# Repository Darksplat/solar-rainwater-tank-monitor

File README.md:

**Fabrication correction — 11 November 2026.** Review found that LOOP_P named both the pressure-probe terminal and the filtered positive measurement input in revision 0.2. This can bypass part of the current-limiting network through a sense resistor. The revision 0.2 PCB and manufacturing exports are superseded and require correction before fabrication. Revision 0.3 development separates the input as LOOP_SENSE_P and adds an explicit netlist check.

# Solar rainwater tank monitor

Development revision 0.2, 9 November 2026. **Engineering prototype; not released for manufacture or installation.** Two independent solar nodes; ESP32-C6, Thread MTD, pressure-loop measurement, ESPHome API to Home Assistant.

The revision includes a routed four-layer KiCad board, ERC/DRC reports, fabrication exports, FreeCAD assembly study, three-monitor firmware and battery/solar alerts. Start with [progress register](docs/progress.md), [architecture](docs/project-overview.md), [research evidence](docs/research.md) and [test report](docs/testing-report.md). Outstanding approvals, missing measurements and physical validation are explicit there. No live Home Assistant system has been modified.

Run `python3 -m unittest discover -s tests/unit -v`, then `python3 tools/power_budget.py`. Compile the shared C++ calculation tests with `c++ -std=c++17 -Wall -Wextra -Werror tests/integration/core_test.cpp -o /tmp/tank-core-test && /tmp/tank-core-test`.

Firmware: copy `firmware/secrets-example.yaml` to ignored `firmware/tank_1/secrets.yaml` and `firmware/tank_2/secrets.yaml`, setting independent real API keys and OTA passwords plus your Thread dataset, then `esphome config firmware/tank_1/tank.yaml` and `esphome compile firmware/tank_1/tank.yaml`; repeat for tank_2. Example secrets are deliberately not deployable credentials. See the installation guide before connecting any transmitter.

No rated capacity is treated as measured usable capacity. Configuration is initially uncalibrated and litres/percentage remain unavailable until calibration is enabled.

Build hardware with the [assembly guide](docs/assembly-guide.md), [electrical connection table](docs/electrical-design.md) and [manufacturing notes](hardware/pcb/manufacturing/README.md). Revision 0.1 binaries and wiring are historical and incompatible with revision 0.2.

Owner configuration is recorded in [site settings](docs/site-configuration.md): garden water, secondary fire use, no minimum-reserve display, catalogue tank height2.32m and the existing Raspberry Pi Zero2W/PoE/Sonoff Thread network. Internal geometry and operating datums remain unverified.

[Revision0.2 test images and checksums](releases/0.2.0-dev/) and [successful hosted validation](docs/publication-validation.md) are available. These are development artifacts; physical hardware and installation acceptance remain pending.

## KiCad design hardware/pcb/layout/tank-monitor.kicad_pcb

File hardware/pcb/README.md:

# PCB release hold

No valid complete schematic, layout, Gerber, drill, CPL or board 3D file exists in this revision. Directories reserve the requested structure. Do not mistake their presence for deliverables.

KiCad CLI 10.0.3 is installed. Live IPC was unavailable. This does not itself prevent offline design; current blockers are incomplete protected input/power design, final component qualification and footprint verification. Do not export an outline-only board and claim it is manufacturable.

Next: select protected receiver and power converters, obtain sensor order drawing, assign every pin/net, complete loop and power fault analysis, create manufacturer-backed symbol/footprint library, draw schematic, run ERC, route layout with antenna keepout, run DRC/unconnected checks, then export fabrication and assembly package and prototype.

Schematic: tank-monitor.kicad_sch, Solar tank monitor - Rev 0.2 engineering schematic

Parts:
C1: 10u 50V X7R; C_1210_3225Metric; MPN C3225X7R1H106K250AC
C2: 100n 50V; C_0603_1608Metric; MPN C1608X7R1H104K080AA
C3: 100n 16V; C_0603_1608Metric; MPN C1608X7R1H104K080AA
C4, C5: 22u 16V X7R; C_1210_3225Metric; MPN C3225X7R1C226M250AC
C6: 4.7u 16V X7R; C_0805_2012Metric; MPN C2012X7R1C475K125AB
C7: 4.7u 50V X7R; C_1210_3225Metric; MPN C3225X7R1H475K250AB
C8: 10n; C_0603_1608Metric; MPN C1608X7R1H103K080AA
C20, C30, C40: 100n 100V; C_0805_2012Metric; MPN C2012X7R2A104K125AA
C21, C31, C41, C52: 100n; C_0603_1608Metric; MPN C1608X7R1H104K080AA
C50: 1u; C_0603_1608Metric; MPN C1608X7R1C105K080AC
C51: 10u 35V X5R; C_0805_2012Metric; MPN C2012X5R1V106K085AC
D1, D3: B360A-13-F; D_SMA; MPN B360A-13-F
D2: SMBJ15A; D_SMB; MPN SMBJ15A
D4: SMBJ18A; D_SMB; MPN SMBJ18A
D5, D6, D7: SMBJ51A; D_SMB; MPN SMBJ51A
D8: STATUS; LED_0603_1608Metric; MPN LTST-C190KGKT
D9: 1N5408; 1N5408_DO201AD_P20.32; MPN 1N5408-E3/54
D10: 1N4148W-7-F; D_SOD-123; MPN 1N4148W-7-F
J1: BATTERY FUSED 5A; TerminalBlock_Phoenix_MKDS-1,5-2-5.08_1x02_P5.08mm_Horizont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; MPN Phoenix 1715721
J2: CHARGER BAT; TerminalBlock_Phoenix_MKDS-1,5-2-5.08_1x02_P5.08mm_Horizont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; MPN Phoenix 1715721
J3: PROTECTED LOAD; TerminalBlock_Phoenix_MKDS-1,5-2-5.08_1x02_P5.08mm_Horizont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; MPN Phoenix 1715721
J4: PV INPUT; TerminalBlock_Phoenix_MKDS-1,5-2-5.08_1x02_P5.08mm_Horizont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; MPN Phoenix 1715721
J5: CHARGER PV; TerminalBlock_Phoenix_MKDS-1,5-2-5.08_1x02_P5.08mm_Horizont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; MPN Phoenix 1715721
J6: PRESSURE LOOP; TerminalBlock_Phoenix_MKDS-1,5-2-5.08_1x02_P5.08mm_Horizont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; MPN Phoenix 1715721
J7: UART 3.3V ONLY; PinHeader_1x06_P2.54mm_Vertical; MPN TSW-106-07-G-S
L1: 4.7uH Isat>=4A; L_Bourns_SRP5030T; MPN SRP5030TA-4R7M
L2: 10uH Isat>=1.6A; L_Bourns_SRP5030T; MPN SRP5030TA-100M
Q1: DMP2035U-7; SOT-23; MPN DMP2035U-7
Q2, Q3: IPD50N06S4L-12; TO-252-2; MPN IPD50N06S4L12ATMA2
Q4: BC847B-7-F; SOT-23; MPN BC847B-7-F
R1: 0.01R 1% 1W; R_2512_6332Metric; MPN WSL2512R0100FEA
R2: 0.02R 1% 1W; R_2512_6332Metric; MPN WSL2512R0200FEA
R3, R4, R5, R10, R65, R66: 100k; R_0603_1608Metric; MPN RC0603FR-07100KL
R6: 1k; R_0603_1608Metric; MPN RC0603FR-071KL
R7: 130k 0.1%; R_0603_1608Metric; MPN RT0603BRD07130KL
R8: 10k 0.1%; R_0603_1608Metric; MPN RT0603BRD0710KL
R9: 4.99k; R_0603_1608Metric; MPN RC0603FR-074K99L
R11: 2R 0.1% 25ppm; R_1206_3216Metric; MPN RT1206BRD072RL
R12, R13: 110R 1.5W; R_2512_6332Metric; MPN CRCW2512110RFKEGHP
R20, R21, R22, R40, R41, R42: 10R; R_0603_1608Metric; MPN RC0603FR-0710RL
R30, R31, R32: 47R; R_0603_1608Metric; MPN RC0603FR-0747RL
R50, R51: 4.7k; R_0603_1608Metric; MPN RC0603FR-074K7L
R52, R53, R54, R64, R67: 10k; R_0603_1608Metric; MPN RC0603FR-0710KL
R55: 2.2k; R_0603_1608Metric; MPN RC0603FR-072K2L
R60: 2.74M; R_0603_1608Metric; MPN RC0603FR-072M74L
R61: 215k; R_0603_1608Metric; MPN RC0603FR-07215KL
R62: 84.5k; R_0603_1608Metric; MPN RC0603FR-0784K5L
R63: 510k; R_0603_1608Metric; MPN RC0603FR-07510KL
SW1: RESET; SW_SPST_TL3342; MPN TL3342F160QG-TR
SW2: BOOT; SW_SPST_TL3342; MPN TL3342F160QG-TR
TP1: GND; TestPoint_Pad_D2.0mm
TP2: V3V3; TestPoint_Pad_D2.0mm
TP3: VIN; TestPoint_Pad_D2.0mm
TP4: LOOP_SUPPLY; TestPoint_Pad_D2.0mm
TP5: LOOP_P; TestPoint_Pad_D2.0mm
TP6: SDA; TestPoint_Pad_D2.0mm
TP7: SCL; TestPoint_Pad_D2.0mm
TP8: BAT_FUSED; TestPoint_Pad_D2.0mm
TP9: CHARGER_BAT; TestPoint_Pad_D2.0mm
TP10: PV_IN; TestPoint_Pad_D2.0mm
TP11: PV_OUT; TestPoint_Pad_D2.0mm
TP12: LOOP_EN_N; TestPoint_Pad_D2.0mm
U1: AP63203WU-7; TSOT-23-6; MPN AP63203WU-7
U2: TPS61170DRVR; WSON-6-1EP_2x2mm_P0.65mm_EP1x1.6mm; MPN TPS61170DRVR
U3, U4, U5: INA228AIDGSR; TSSOP-10_3x3mm_P0.5mm; MPN INA228AIDGSR
U6: ESP32-C6-MINI-1-N4; ESP32-C6-MINI-1-edge-silk; MPN ESP32-C6-MINI-1-N4
U7: LTC4365ITS8#TRMPBF; TSOT-23-8; MPN LTC4365ITS8#TRMPBF

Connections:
BAT_FUSED: Q3.2 (D), R1.1, R20.1, R22.1, TP8.1, U7.7 (Vout)
BAT_N: C20.2, R21.2, U3.9 (Vin-)
BAT_P: C20.1, R20.2, U3.10 (Vin+)
BAT_RAW: J1.1, Q2.2 (D), R60.1, R63.1, R65.1, U7.1 (Vin)
BAT_VBUS: R22.2, U3.8 (Vbus)
BOOST_GATE: Q1.1 (G), R5.1, R6.2
BOOST_IN: C6.1, L2.1, Q1.3 (D), U2.5 (CTRL), U2.6 (VIN)
BOOT: J7.5, R53.2, SW2.1, U6.23 (IO9)
BST: C3.1, U1.6 (BST)
CHARGER_BAT: J2.1, R1.2, R21.1, TP9.1
COMP: R9.1, U2.2 (COMP)
COMP_RC: C8.1, R9.2
EN: C50.1, J7.6, R52.2, SW1.1, U6.8 (EN)
EN_BUCK: R3.2, R4.1, U1.2 (EN)
FB_BOOST: R7.2, R8.1, U2.1 (FB)
GND: C1.2, C2.2, C4.2, C5.2, C6.2, C7.2, C8.2, C21.2, C31.2, C41.2, C50.2, C51.2, C52.2, D2.2 (A), D4.2 (A), D5.2 (A), D6.2 (A), D7.2 (A), D10.2 (A), J1.2, J2.2, J3.2, J6.2, J7.1, Q4.2 (E), R4.2, R8.2, R10.2, R62.2, R67.2, SW1.2, SW2.2, TP1.1, U1.4 (GND), U2.3 (GND), U2.7 (PAD), U3.1 (A1), U3.2 (A0), U3.7 (GND), U4.1 (A1), U4.7 (GND), U5.1 (A1), U5.7 (GND), U6.1 (GND), U6.2 (GND), U6.11 (GND), U6.14 (GND), U6.36 (GND), U6.37 (GND), U6.38 (GND), U6.39 (GND), U6.40 (GND), U6.41 (GND), U6.42 (GND), U6.43 (GND), U6.44 (GND), U6.45 (GND), U6.46 (GND), U6.47 (GND), U6.48 (GND), U6.49 (GND), U6.50 (GND), U6.51 (GND), U6.52 (GND), U6.53 (GND), U7.4 (GND)
LED_A: D8.2 (A), R55.2
LED_K: D8.1 (K), U6.24 (IO18)
LOAD_IN: D1.2 (A), J3.1
LOOP_EN_N: R6.1, TP12.1, U6.9 (IO4)
LOOP_LIMIT_MID: R12.2, R13.1
LOOP_N: C40.2, R41.2, U5.9 (Vin-)
LOOP_P: C40.1, J6.1, R13.2, R40.2, R42.1, TP5.1, U5.10 (Vin+)
LOOP_SHUNT_OUT: R11.2, R12.1, R41.1
LOOP_SUPPLY: C7.1, D3.1 (K), D4.1 (K), R7.1, R10.1, R11.1, R40.1, TP4.1
LOOP_VBUS: R42.2, U5.8 (Vbus)
PV_IN: D9.1 (K), R2.1, R30.1, TP10.1
PV_N: C30.2, D6.1 (K), R31.2, U4.9 (Vin-)
PV_NEG: J4.2, J5.2
PV_OUT: J5.1, R2.2, R31.1, R32.1, TP11.1
PV_P: C30.1, D5.1 (K), R30.2, U4.10 (Vin+)
PV_RAW: D9.2 (A), J4.1
PV_VBUS: D7.1 (K), R32.2, U4.8 (Vbus)
RAW_BASE: D10.1 (K), Q4.1 (B), R65.2, R67.1
RAW_PRESENT: Q4.3 (C), R66.2, U6.26 (IO20)
REV_FAULT: R64.2, U6.25 (IO19), U7.6 (~FAULT)
REV_GATE: Q2.1 (G), Q3.1 (G), U7.8 (GATE)
REV_OV: R61.2, R62.1, U7.3 (OV)
REV_SHDN: R63.2, U7.5 (~SHDN)
REV_SOURCE: Q2.3 (S), Q3.3 (S)
REV_UV: R60.2, R61.1, U7.2 (UV)
RXD: J7.4, U6.30 (RXD0)
SCL: R51.2, TP7.1, U3.5 (SCL), U4.5 (SCL), U5.5 (SCL), U6.16 (IO7)
SDA: R50.2, TP6.1, U3.4 (SDA), U4.4 (SDA), U5.2 (A0), U5.4 (SDA), U6.15 (IO6)
STRAP8: R54.2, U6.22 (IO8)
SW_BOOST: D3.2 (A), L2.2, U2.4 (SW)
SW_BUCK: C3.2, L1.1, U1.5 (SW)
TXD: J7.3, U6.31 (TXD0)
V3V3: C4.1, C5.1, C21.1, C31.1, C41.1, C51.1, C52.1, J7.2, L1.2, Q1.2 (S), R5.2, R50.1, R51.1, R52.1, R53.1, R54.1, R55.1, R64.1, R66.1, TP2.1, U1.1 (FB), U3.6 (VS), U4.2 (A0), U4.6 (VS), U5.6 (VS), U6.3 (3V3)
VIN: C1.1, C2.1, D1.1 (K), D2.1 (K), R3.1, TP3.1, U1.3 (IN)

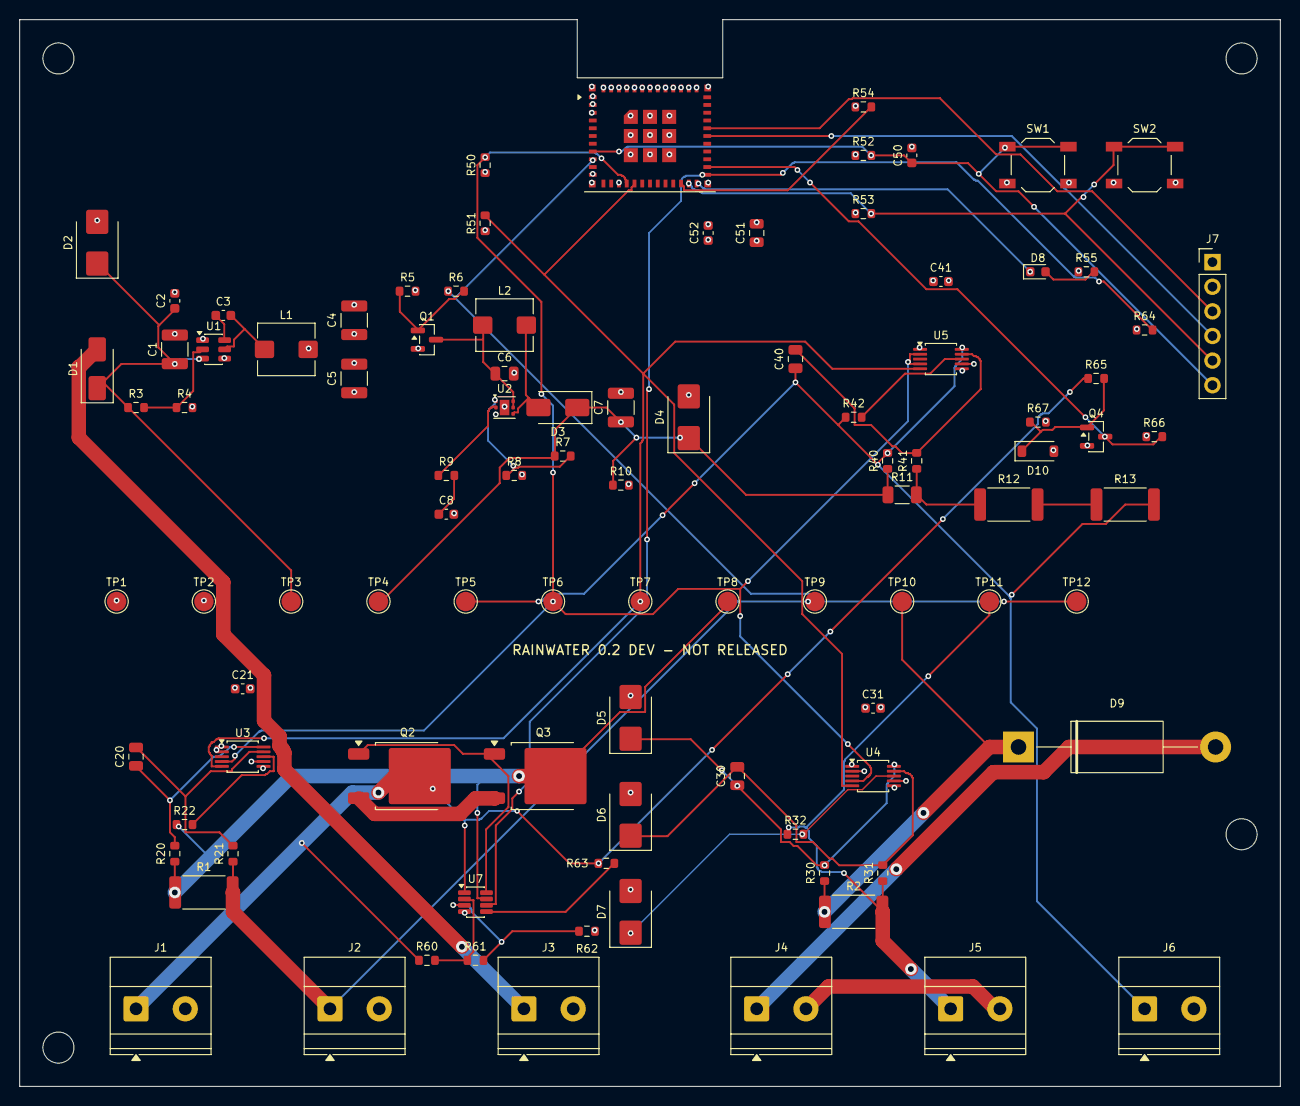
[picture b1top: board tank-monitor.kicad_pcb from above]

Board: 4 copper layers, 130.0 x 110.0 mm, 101 parts (0 on the bottom side), 50 nets.

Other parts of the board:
H1, H2, H3, H4: MountingHole_3.2mm_M3

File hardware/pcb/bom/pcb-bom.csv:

Reference,Value,Footprint,MPN,Quantity for two boards
J1,BATTERY FUSED 5A,"TerminalBlock_Phoenix:TerminalBlock_Phoenix_MKDS-1,5-2-5.08_1x02_P5.08mm_Horizontal",Phoenix 1715721,2
J2,CHARGER BAT,"TerminalBlock_Phoenix:TerminalBlock_Phoenix_MKDS-1,5-2-5.08_1x02_P5.08mm_Horizontal",Phoenix 1715721,2
J3,PROTECTED LOAD,"TerminalBlock_Phoenix:TerminalBlock_Phoenix_MKDS-1,5-2-5.08_1x02_P5.08mm_Horizontal",Phoenix 1715721,2
J4,PV INPUT,"TerminalBlock_Phoenix:TerminalBlock_Phoenix_MKDS-1,5-2-5.08_1x02_P5.08mm_Horizontal",Phoenix 1715721,2
J5,CHARGER PV,"TerminalBlock_Phoenix:TerminalBlock_Phoenix_MKDS-1,5-2-5.08_1x02_P5.08mm_Horizontal",Phoenix 1715721,2
J6,PRESSURE LOOP,"TerminalBlock_Phoenix:TerminalBlock_Phoenix_MKDS-1,5-2-5.08_1x02_P5.08mm_Horizontal",Phoenix 1715721,2
U7,LTC4365ITS8#TRMPBF,Package_TO_SOT_SMD:TSOT-23-8,LTC4365ITS8#TRMPBF,2
Q2,IPD50N06S4L-12,Package_TO_SOT_SMD:TO-252-2,IPD50N06S4L12ATMA2,2
Q3,IPD50N06S4L-12,Package_TO_SOT_SMD:TO-252-2,IPD50N06S4L12ATMA2,2
R60,2.74M,Resistor_SMD:R_0603_1608Metric,RC0603FR-072M74L,2
R61,215k,Resistor_SMD:R_0603_1608Metric,RC0603FR-07215KL,2
R62,84.5k,Resistor_SMD:R_0603_1608Metric,RC0603FR-0784K5L,2
R63,510k,Resistor_SMD:R_0603_1608Metric,RC0603FR-07510KL,2
R64,10k,Resistor_SMD:R_0603_1608Metric,RC0603FR-0710KL,2
D9,1N5408,TankMonitor:1N5408_DO201AD_P20.32,1N5408-E3/54,2
Q4,BC847B-7-F,Package_TO_SOT_SMD:SOT-23,BC847B-7-F,2
R65,100k,Resistor_SMD:R_0603_1608Metric,RC0603FR-07100KL,2
R66,100k,Resistor_SMD:R_0603_1608Metric,RC0603FR-07100KL,2
R67,10k,Resistor_SMD:R_0603_1608Metric,RC0603FR-0710KL,2
D10,1N4148W-7-F,Diode_SMD:D_SOD-123,1N4148W-7-F,2
R1,0.01R 1% 1W,Resistor_SMD:R_2512_6332Metric,WSL2512R0100FEA,2
R2,0.02R 1% 1W,Resistor_SMD:R_2512_6332Metric,WSL2512R0200FEA,2
D1,B360A-13-F,Diode_SMD:D_SMA,B360A-13-F,2
D2,SMBJ15A,Diode_SMD:D_SMB,SMBJ15A,2
U1,AP63203WU-7,Package_TO_SOT_SMD:TSOT-23-6,AP63203WU-7,2
R3,100k,Resistor_SMD:R_0603_1608Metric,RC0603FR-07100KL,2
R4,100k,Resistor_SMD:R_0603_1608Metric,RC0603FR-07100KL,2
C1,10u 50V X7R,Capacitor_SMD:C_1210_3225Metric,C3225X7R1H106K250AC,2
C2,100n 50V,Capacitor_SMD:C_0603_1608Metric,C1608X7R1H104K080AA,2
C3,100n 16V,Capacitor_SMD:C_0603_1608Metric,C1608X7R1H104K080AA,2
L1,4.7uH Isat>=4A,Inductor_SMD:L_Bourns_SRP5030T,SRP5030TA-4R7M,2
C4,22u 16V X7R,Capacitor_SMD:C_1210_3225Metric,C3225X7R1C226M250AC,2
C5,22u 16V X7R,Capacitor_SMD:C_1210_3225Metric,C3225X7R1C226M250AC,2
Q1,DMP2035U-7,Package_TO_SOT_SMD:SOT-23,DMP2035U-7,2
R5,100k,Resistor_SMD:R_0603_1608Metric,RC0603FR-07100KL,2
R6,1k,Resistor_SMD:R_0603_1608Metric,RC0603FR-071KL,2
U2,TPS61170DRVR,Package_SON:WSON-6-1EP_2x2mm_P0.65mm_EP1x1.6mm,TPS61170DRVR,2
C6,4.7u 16V X7R,Capacitor_SMD:C_0805_2012Metric,C2012X7R1C475K125AB,2
L2,10uH Isat>=1.6A,Inductor_SMD:L_Bourns_SRP5030T,SRP5030TA-100M,2
D3,B360A-13-F,Diode_SMD:D_SMA,B360A-13-F,2
C7,4.7u 50V X7R,Capacitor_SMD:C_1210_3225Metric,C3225X7R1H475K250AB,2
R7,130k 0.1%,Resistor_SMD:R_0603_1608Metric,RT0603BRD07130KL,2
R8,10k 0.1%,Resistor_SMD:R_0603_1608Metric,RT0603BRD0710KL,2
R9,4.99k,Resistor_SMD:R_0603_1608Metric,RC0603FR-074K99L,2
C8,10n,Capacitor_SMD:C_0603_1608Metric,C1608X7R1H103K080AA,2
R10,100k,Resistor_SMD:R_0603_1608Metric,RC0603FR-07100KL,2
D4,SMBJ18A,Diode_SMD:D_SMB,SMBJ18A,2
R11,2R 0.1% 25ppm,Resistor_SMD:R_1206_3216Metric,RT1206BRD072RL,2
R12,110R 1.5W,Resistor_SMD:R_2512_6332Metric,CRCW2512110RFKEGHP,2
R13,110R 1.5W,Resistor_SMD:R_2512_6332Metric,CRCW2512110RFKEGHP,2
U3,INA228AIDGSR,Package_SO:TSSOP-10_3x3mm_P0.5mm,INA228AIDGSR,2
R20,10R,Resistor_SMD:R_0603_1608Metric,RC0603FR-0710RL,2
R21,10R,Resistor_SMD:R_0603_1608Metric,RC0603FR-0710RL,2
R22,10R,Resistor_SMD:R_0603_1608Metric,RC0603FR-0710RL,2
C20,100n 100V,Capacitor_SMD:C_0805_2012Metric,C2012X7R2A104K125AA,2
C21,100n,Capacitor_SMD:C_0603_1608Metric,C1608X7R1H104K080AA,2
U4,INA228AIDGSR,Package_SO:TSSOP-10_3x3mm_P0.5mm,INA228AIDGSR,2
R30,47R,Resistor_SMD:R_0603_1608Metric,RC0603FR-0747RL,2
R31,47R,Resistor_SMD:R_0603_1608Metric,RC0603FR-0747RL,2
R32,47R,Resistor_SMD:R_0603_1608Metric,RC0603FR-0747RL,2
C30,100n 100V,Capacitor_SMD:C_0805_2012Metric,C2012X7R2A104K125AA,2
C31,100n,Capacitor_SMD:C_0603_1608Metric,C1608X7R1H104K080AA,2
D5,SMBJ51A,Diode_SMD:D_SMB,SMBJ51A,2
D6,SMBJ51A,Diode_SMD:D_SMB,SMBJ51A,2
D7,SMBJ51A,Diode_SMD:D_SMB,SMBJ51A,2
U5,INA228AIDGSR,Package_SO:TSSOP-10_3x3mm_P0.5mm,INA228AIDGSR,2
R40,10R,Resistor_SMD:R_0603_1608Metric,RC0603FR-0710RL,2
R41,10R,Resistor_SMD:R_0603_1608Metric,RC0603FR-0710RL,2
R42,10R,Resistor_SMD:R_0603_1608Metric,RC0603FR-0710RL,2
C40,100n 100V,Capacitor_SMD:C_0805_2012Metric,C2012X7R2A104K125AA,2
C41,100n,Capacitor_SMD:C_0603_1608Metric,C1608X7R1H104K080AA,2
U6,ESP32-C6-MINI-1-N4,TankMonitor:ESP32-C6-MINI-1-edge-silk,ESP32-C6-MINI-1-N4,2
R50,4.7k,Resistor_SMD:R_0603_1608Metric,RC0603FR-074K7L,2
R51,4.7k,Resistor_SMD:R_0603_1608Metric,RC0603FR-074K7L,2
R52,10k,Resistor_SMD:R_0603_1608Metric,RC0603FR-0710KL,2
C50,1u,Capacitor_SMD:C_0603_1608Metric,C1608X7R1C105K080AC,2
R53,10k,Resistor_SMD:R_0603_1608Metric,RC0603FR-0710KL,2
R54,10k,Resistor_SMD:R_0603_1608Metric,RC0603FR-0710KL,2
C51,10u 35V X5R,Capacitor_SMD:C_0805_2012Metric,C2012X5R1V106K085AC,2
C52,100n,Capacitor_SMD:C_0603_1608Metric,C1608X7R1H104K080AA,2
SW1,RESET,Button_Switch_SMD:SW_SPST_TL3342,TL3342F160QG-TR,2
SW2,BOOT,Button_Switch_SMD:SW_SPST_TL3342,TL3342F160QG-TR,2
J7,UART 3.3V ONLY,Connector_PinHeader_2.54mm:PinHeader_1x06_P2.54mm_Vertical,TSW-106-07-G-S,2
D8,STATUS,LED_SMD:LED_0603_1608Metric,LTST-C190KGKT,2
R55,2.2k,Resistor_SMD:R_0603_1608Metric,RC0603FR-072K2L,2
TP1,GND,TestPoint:TestPoint_Pad_D2.0mm,,2
TP2,V3V3,TestPoint:TestPoint_Pad_D2.0mm,,2
TP3,VIN,TestPoint:TestPoint_Pad_D2.0mm,,2
TP4,LOOP_SUPPLY,TestPoint:TestPoint_Pad_D2.0mm,,2
TP5,LOOP_P,TestPoint:TestPoint_Pad_D2.0mm,,2
TP6,SDA,TestPoint:TestPoint_Pad_D2.0mm,,2
TP7,SCL,TestPoint:TestPoint_Pad_D2.0mm,,2
TP8,BAT_FUSED,TestPoint:TestPoint_Pad_D2.0mm,,2
TP9,CHARGER_BAT,TestPoint:TestPoint_Pad_D2.0mm,,2
TP10,PV_IN,TestPoint:TestPoint_Pad_D2.0mm,,2
TP11,PV_OUT,TestPoint:TestPoint_Pad_D2.0mm,,2
TP12,LOOP_EN_N,TestPoint:TestPoint_Pad_D2.0mm,,2

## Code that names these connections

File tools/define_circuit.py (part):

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   add('D'+str(num),'Device:D_Zener','SMBJ51A','Diode_SMD:D_SMB',{1:net,2:'GND'},'pv','SMBJ51A')
# Module nets assigned by pin NAME by generator, not assumed DevKit pin order.
add('U6','RF_Module:ESP32-C6-MINI-1','ESP32-C6-MINI-1-N4','TankMonitor:ESP32-C6-MINI-1-edge-silk',{},'controller','ESP32-C6-MINI-1-N4','https://www.espressif.com/sites/default/files/documentation/esp32-c6-mini-1_mini-1u_datasheet_en.pdf')
parts[-1]['named_nets']={'GND':'GND','3V3':'V3V3','EN':'EN','GPIO6':'SDA','GPIO7':'SCL','GPIO4':'LOOP_EN_N','GPIO9':'BOOT','GPIO8':'STRAP8','TXD0':'TXD','RXD0':'RXD','GPIO12':None,'GPIO13':None}
res('R50','4.7k','V3V3','SDA','controller');res('R51','4.7k','V3V3','SCL','controller')
res('R52','10k','V3V3','EN','controller');cap('C50','1u','EN','GND','controller')
res('R53','10k','V3V3','BOOT','controller');res('R54','10k','V3V3','STRAP8','controller')
cap('C51','10u 35V X5R','V3V3','GND','controller','Capacitor_SMD:C_0805_2012Metric');cap('C52','100n','V3V3','GND','controller')
for ref,net in [('SW1','EN'),('SW2','BOOT')]:add(ref,'Switch:SW_Push','RESET' if ref=='SW1' else 'BOOT','Button_Switch_SMD:SW_SPST_TL3342',{1:net,2:'GND'},'controller','TL3342F160QG-TR')
add('J7','Connector_Generic:Conn_01x06','UART 3.3V ONLY','Connector_PinHeader_2.54mm:PinHeader_1x06_P2.54mm_Vertical',{1:'GND',2:'V3V3',3:'TXD',4:'RXD',5:'BOOT',6:'EN'},'controller','2.54mm 1x6 header')
add('D8','Device:LED','STATUS','LED_SMD:LED_0603_1608Metric',{1:'LED_K',2:'LED_A'},'controller','LTST-C190KGKT')
res('R55','2.2k','V3V3','LED_A','controller')
# Sink LED from spare GPIO18; no permanently lit power LED.
parts[[i for i,c in enumerate(parts) if c['ref']=='U6'][0]]['named_nets']['GPIO18']='LED_K'
parts[[i for i,c in enumerate(parts) if c['ref']=='U6'][0]]['named_nets']['GPIO19']='REV_FAULT'
parts[[i for i,c in enumerate(parts) if c['ref']=='U6'][0]]['named_nets']['GPIO20']='RAW_PRESENT'
for i,net in enumerate(['GND','V3V3','VIN','LOOP_SUPPLY','LOOP_P','SDA','SCL','BAT_FUSED','CHARGER_BAT','PV_IN','PV_OUT','LOOP_EN_N'],1):
 add('TP'+str(i),'Connector:TestPoint',net,'TestPoint:TestPoint_Pad_D2.0mm',{1:net},'test')
# Exact passive candidates; procurement status and DC-bias gates are recorded separately.
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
